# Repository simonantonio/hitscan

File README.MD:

# Project Hitscan

An attempt at a super cheap time keeping system for racers
It uses IR diodes on a drone, and a detection station to track when the drone passes the detector.

*Should?* be good at up to speeds of 200km/hr with a 200mm detection window - (need to actually validate this)

### IR Details
**Packet timing now:**

* SYNC: 270μs burst + 900μs gap = 1170μs
* 3 bits: ~300-600μs each = ~1200μs average
* **Total: ~2.3ms per packet**

**At 200mm cone width:**

* 100 km/hr (27.78 m/s): 7.2ms window = 3 packets ✅
* 150 km/hr (41.67 m/s): 4.8ms window = 2 packets ✅
* 200 km/hr: 3.6ms window = 1 packet ✅

> [!CAUTION]
> In development

Initial project is currently in the mail from the board fab.

## Tools

* Kicad 9.0 for board development
* PlatformIO for firmware builds and deployment

## Firmware
* [Base station](./hitscan-base/README.MD)
* [IR Blaster](./hitscan/README.MD)

### Web App

## Hardware

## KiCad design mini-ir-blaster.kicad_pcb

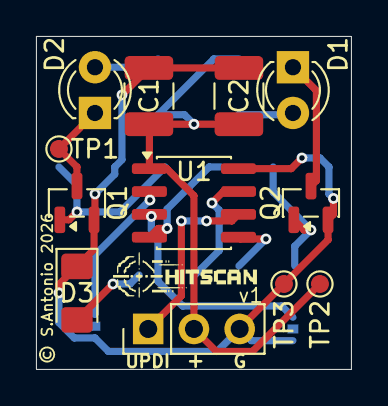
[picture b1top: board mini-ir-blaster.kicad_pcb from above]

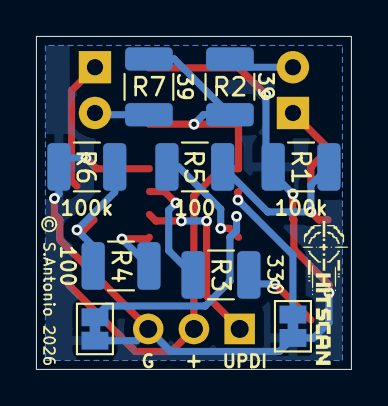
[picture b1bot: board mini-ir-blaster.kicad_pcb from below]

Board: 2 copper layers, 17.5 x 18.5 mm, 21 parts (9 on the bottom side), 15 nets.

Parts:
C1: 10uF; C_1210_3225Metric_Pad1.33x2.70mm_HandSolder
C2: 0.1uF; C_1210_3225Metric_Pad1.33x2.70mm_HandSolder
D1, D2: TSAL4400; LED_D3.0mm_IRBlack
D3: LED; LED_1206_3216Metric_Pad1.42x1.75mm_HandSolder
J1: Conn_01x03_Pin; PinHeader_1x03_P2.54mm_Vertical
JP2, JP3: Jumper_2_Bridged; SolderJumper-2_P1.3mm_Bridged_Pad1.0x1.5mm
Q1, Q2: AO3400A; SOT-23
R1, R6: 100k; R_1210_3225Metric_Pad1.30x2.65mm_HandSolder
R2, R7: 39; R_1210_3225Metric_Pad1.30x2.65mm_HandSolder
R3: 330; R_1210_3225Metric_Pad1.30x2.65mm_HandSolder
R4, R5: 100; R_1210_3225Metric_Pad1.30x2.65mm_HandSolder
TP1: IR1TP; TestPoint_Pad_D1.0mm
TP2: +TP; TestPoint_Pad_D1.0mm
TP3: GNDTP; TestPoint_Pad_D1.0mm
U1: ATtiny402-SS; SOIC-8_3.9x4.9mm_P1.27mm

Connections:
+5V: C1.1, C2.1, J1.2, R2.1, R7.1, TP2.1, U1.1 (VCC)
/PA1: R5.1, U1.4 (PA1)
/PA2: R4.1, U1.5 (PA2)
/UPDI: J1.1, U1.6 (~RESET/PA0)
GND: C1.2, C2.2, D3.1 (K), J1.3, JP2.2 (B), JP3.2 (B), Q1.2 (S), Q2.2 (S), R1.1, R6.1, TP3.1, U1.8 (GND)
unnamed: D1.2 (A), R7.2
unnamed: D1.1 (K), Q2.3 (D)
unnamed: D2.2 (A), R2.2
unnamed: D2.1 (K), Q1.3 (D), TP1.1
unnamed: D3.2 (A), R3.2
unnamed: JP2.1 (A), U1.2 (PA6)
unnamed: JP3.1 (A), U1.3 (PA7)
unnamed: Q1.1 (G), R1.2, R5.2
unnamed: Q2.1 (G), R4.2, R6.2
unnamed: R3.1, U1.7 (PA3)

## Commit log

2026-01-20 initial code checking
2026-01-20 update to run IR detection on seperate core
2026-01-20 basic docs

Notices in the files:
mini-ir-blaster.kicad_pcb:
© S.Antonio 2026
